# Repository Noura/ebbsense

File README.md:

# EBB Sense
  Controlling a wearable display using a bitalino EDA sensor

### Software
- Arduino Code

### Serial Graph for Debugging
- Graph the data from the arduino code running over Serial port
- Scale using up and down keys

### Hardware

- Eagle schematic and board
- Current version is 2.1

### Shirt

Each pinstripe had about 2-7Ω resistance and received about 450mA from a 3.7V LiPo battery via an Adafruit Powerboost 5V regulator, switching on (100% duty cycle) or off (0%) with a transistor controlled by Arduino pins. Each pinstripe consists of a single conductive thread. Snaps on the inside of the shirt provided removable but secure electrical connections to the thread endpoints. A Bitalino skin conductance sensor was placed on the back of the left shoulder of the shirt to hide the sensor from public view and secure it within the shirt. 

Fabric enclosures for electronics fit inside the shirt. (a) Skin conductance sensor with electrodes on colored paper for visibility. (b) Snaps connections to pinstripes. (c) Diagrammatic representation of pinstripes, which in actuality were sewn into shirt. (d) Snaps connections with FSRs for override on/off features. (e) Diagrammatic representation of FSRs, which in actuality were embedded in shirt seams. (f) PCB and battery, which were hidden in an interior shirt pocket.

---

### Team
- Noura Howell
- Laura Devendorf
- Rundong Tian
- Tomás Vega

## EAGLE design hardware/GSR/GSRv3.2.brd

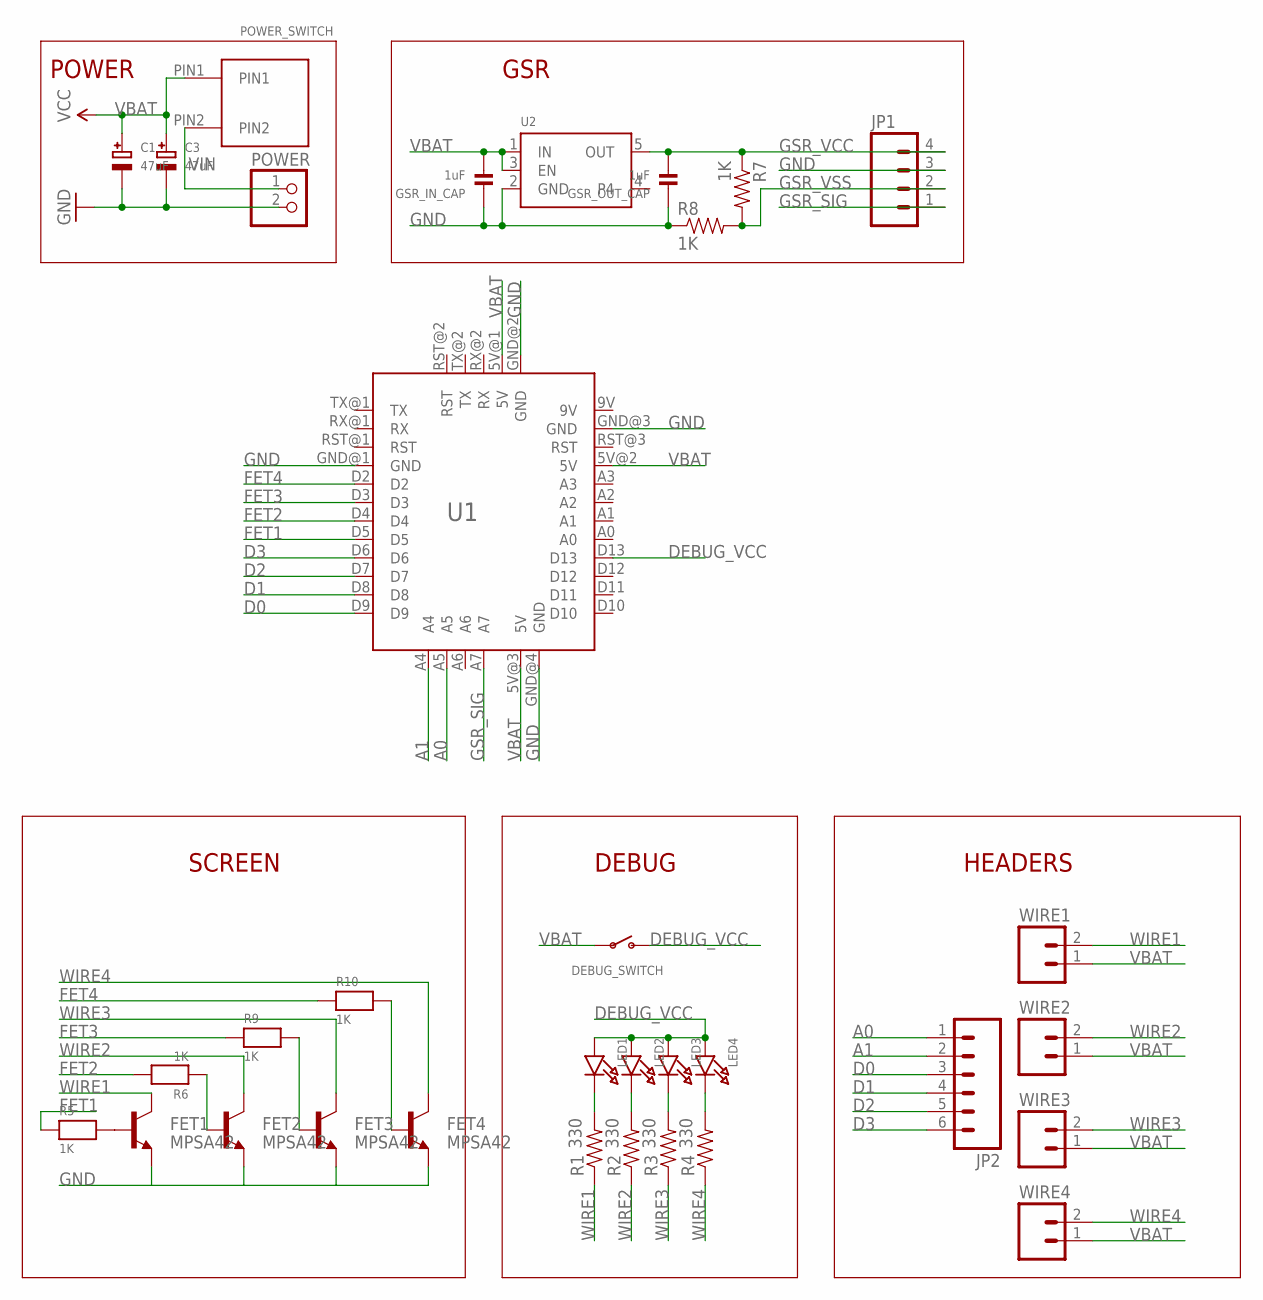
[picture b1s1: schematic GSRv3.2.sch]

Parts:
C1, C3: 47uF; EIA3528-21/B-W
DEBUG_SWITCH: SWITCH_SPST; SPST_SMT_19192
FET1, FET2, FET3, FET4: MPSA42; SOT23-3
GSR_IN_CAP: 1uF; 0603
GSR_OUT_CAP: 1uF; 0603
JP1: M04POLAR; MOLEX-1X4
JP2: M06SILK_FEMALE_PTH; 1X06
LED1, LED2, LED3, LED4: LED0603_NOOUTLINE; CHIPLED_0603_NOOUTLINE
POWER: JST_2PIN; JSTPH2
POWER_SWITCH: PUSH_BUTTON
R1, R2, R3, R4: 330; 0603-RES
R5, R6, R7, R8, R9, R10: 1K; 0603
U1: ARDUINO_MINI
U2: VREG_SOT23-5; SOT23-5
WIRE1, WIRE2, WIRE3, WIRE4: M02POLAR; MOLEX-1X2

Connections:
9V: U1.9V
A0: JP2.1, U1.A5
A1: JP2.2, U1.A4
D0: JP2.3, U1.D9
D1: JP2.4, U1.D8
D2: JP2.5, U1.D7
D3: JP2.6, U1.D6
DEBUG_VCC: DEBUG_SWITCH.C (S), LED1.A, LED2.A, LED3.A, LED4.A, U1.D13
FET1: R5.1, U1.D5
FET2: R6.2, U1.D4
FET3: R9.1, U1.D3
FET4: R10.1, U1.D2
GND: C1.-, C3.-, FET1.2 (E), FET2.2 (E), FET3.2 (E), FET4.2 (E), GSR_IN_CAP.1, GSR_OUT_CAP.1, JP1.3, POWER.2, R8.1, U1.GND@1 (GND), U1.GND@2 (GND), U1.GND@3 (GND), U1.GND@4 (GND), U2.2 (GND)
GSR_SIG: JP1.1, U1.A7
GSR_VCC: GSR_OUT_CAP.2, JP1.4, R7.1, U2.5 (OUT)
GSR_VSS: JP1.2, R7.2, R8.2
unnamed: LED1.C, R1.2
unnamed: LED2.C, R2.2
unnamed: LED3.C, R3.2
unnamed: LED4.C, R4.2
unnamed: FET1.1 (B), R5.2
unnamed: FET2.1 (B), R6.1
unnamed: FET3.1 (B), R9.2
unnamed: FET4.1 (B), R10.2
VBAT: C1.+, C3.+, DEBUG_SWITCH.B, GSR_IN_CAP.2, POWER_SWITCH.PIN1, U1.5V@1 (5V), U1.5V@2 (5V), U1.5V@3 (5V), U2.1 (IN), U2.3 (EN), WIRE1.1, WIRE2.1, WIRE3.1, WIRE4.1
VIN: POWER.1, POWER_SWITCH.PIN2
WIRE1: FET1.3 (C), R1.1, WIRE1.2
WIRE2: FET2.3 (C), R2.1, WIRE2.2
WIRE3: FET3.3 (C), R3.1, WIRE3.2
WIRE4: FET4.3 (C), R4.1, WIRE4.2

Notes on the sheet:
DEBUG
SCREEN
HEADERS
POWER
GSR

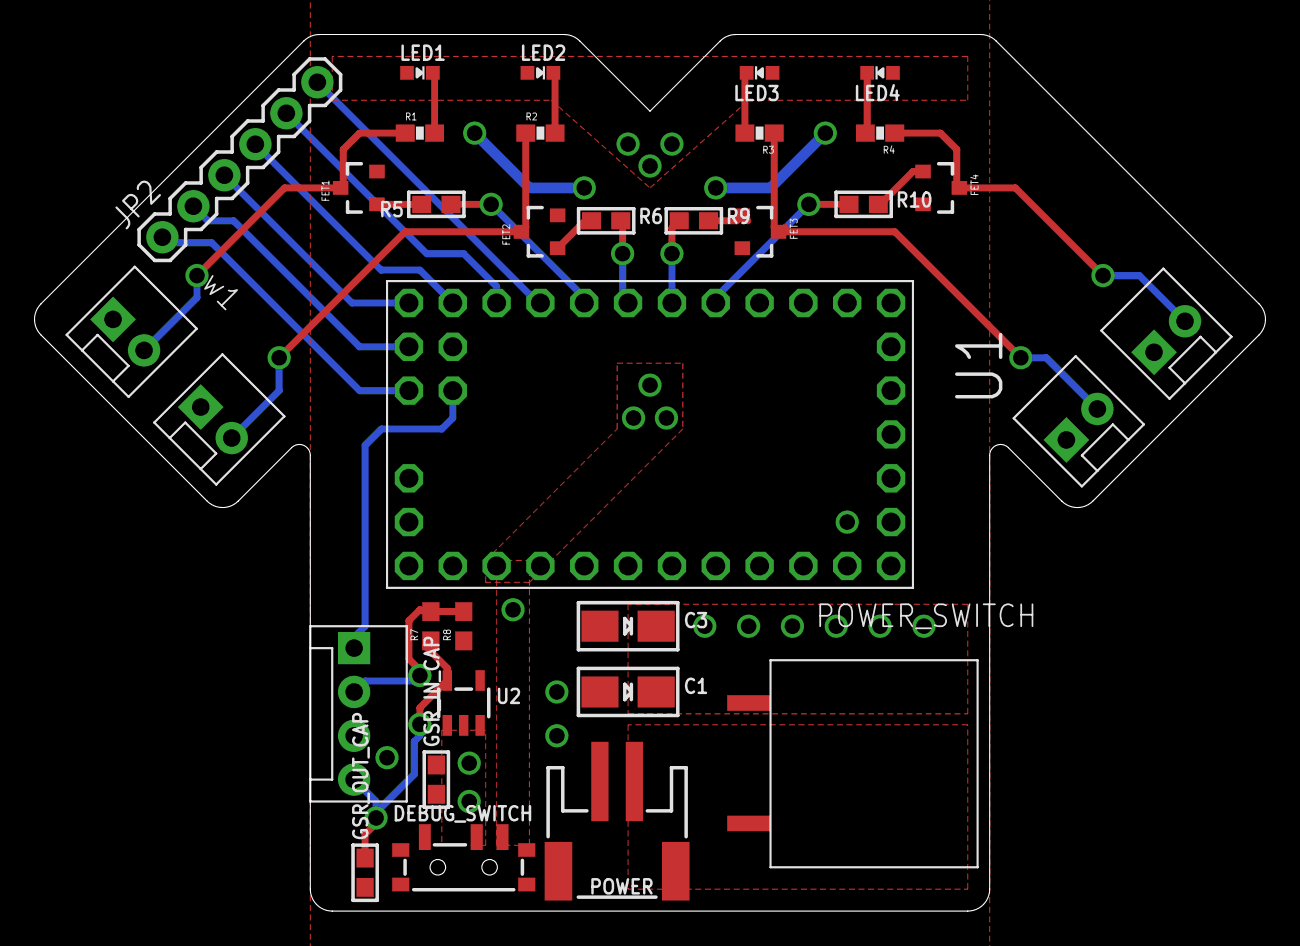
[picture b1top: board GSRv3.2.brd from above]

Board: 2 copper layers, 71.3 x 50.8 mm, 33 parts (0 on the bottom side), 29 nets.

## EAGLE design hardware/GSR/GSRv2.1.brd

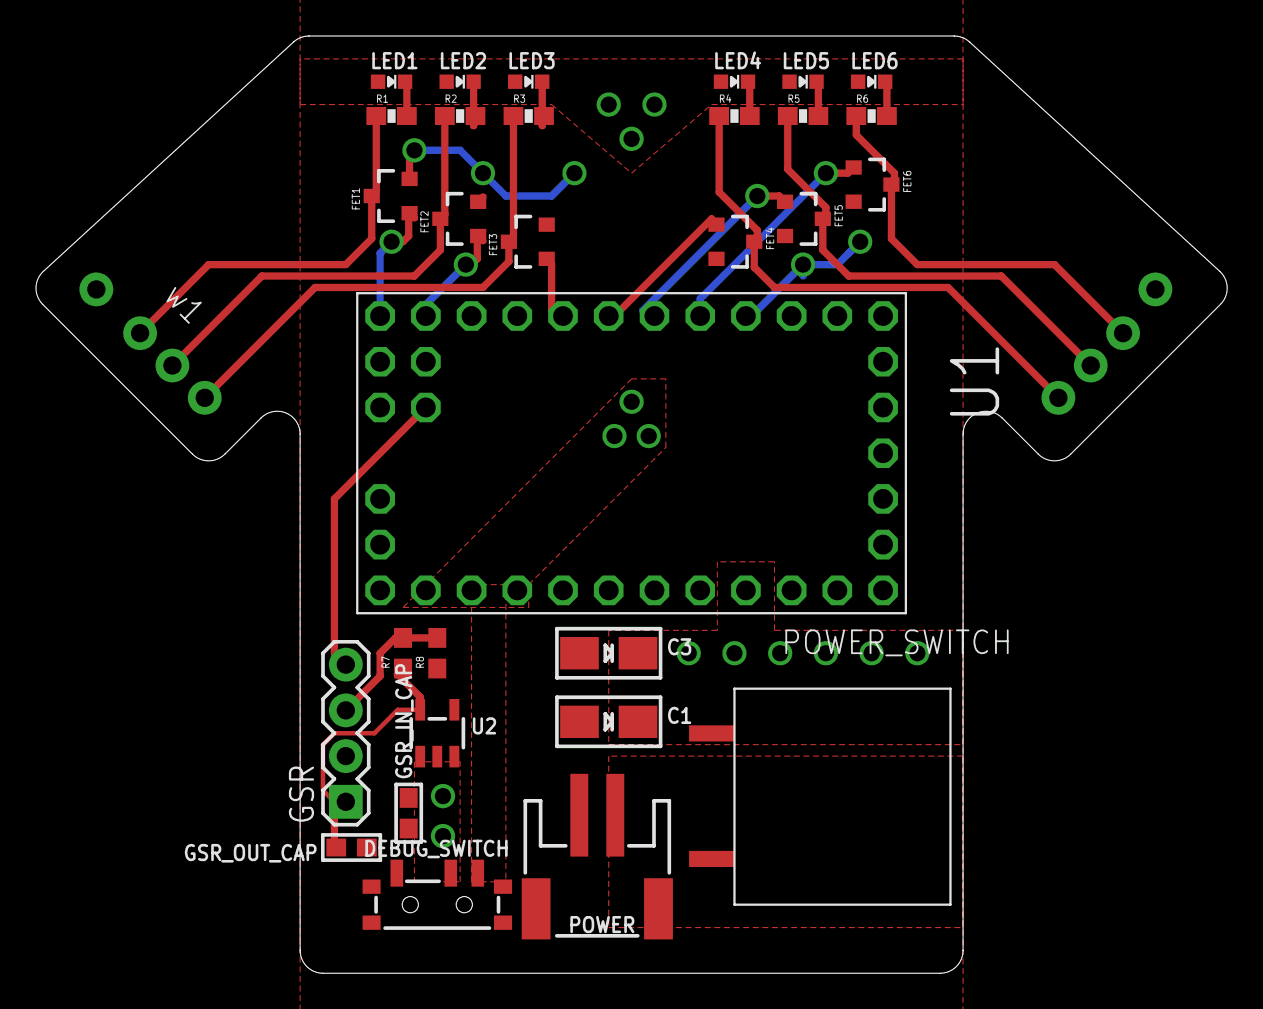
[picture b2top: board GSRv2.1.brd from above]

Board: 2 copper layers, 66.2 x 52.1 mm, 38 parts (0 on the bottom side), 25 nets.

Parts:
C1, C3: EIA3528-21/B-W
DEBUG_SWITCH: SPST_SMT_19192
FET1, FET2, FET3, FET4, FET5, FET6: MPSA42; SOT23-3
GSR: 1X04
GSR_IN_CAP: 1uF; 0603
GSR_OUT_CAP: 1uF; 0603
LED1, LED2, LED3, LED4, LED5, LED6: CHIPLED_0603_NOOUTLINE
POWER: JSTPH2
POWER_SWITCH: PUSH_BUTTON
R1, R2, R3, R4, R5, R6: 330; 0603-RES
R7, R8: 330; 0603
U1: ARDUINO_MINI
U2: SOT23-5
VBAT@1, VBAT@2: 1X01NS-KIT
W1, W2, W3, W4, W5, W6: 1X01NS-KIT

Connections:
DEBUG_VCC: DEBUG_SWITCH.C, LED1.A, LED2.A, LED3.A, LED4.A, LED5.A, LED6.A, U1.D13
FET1: FET1.1, U1.D9
FET2: FET2.1, U1.D8
FET3: FET3.1, U1.D5
FET4: FET4.1, U1.D4
FET5: FET5.1, U1.D3
FET6: FET6.1, U1.D2
GND: C1.-, C3.-, FET1.2, FET2.2, FET3.2, FET4.2, FET5.2, FET6.2, GSR.2, GSR_IN_CAP.1, GSR_OUT_CAP.1, POWER.2, R8.1, U1.GND@1, U1.GND@2, U1.GND@3, U1.GND@4, U2.2
GSR_SIG: GSR.4, U1.A7
GSR_VCC: GSR.1, GSR_OUT_CAP.2, R7.1, U2.5
GSR_VSS: GSR.3, R7.2, R8.2
unnamed: LED1.C, R1.2
unnamed: LED2.C, R2.2
unnamed: LED3.C, R3.2
unnamed: LED4.C, R4.2
unnamed: LED5.C, R5.2
unnamed: LED6.C, R6.2
VBAT: C1.+, C3.+, DEBUG_SWITCH.B, GSR_IN_CAP.2, POWER_SWITCH.PIN1, U1.5V@1, U1.5V@2, U1.5V@3, U2.1, U2.3, VBAT@1.1, VBAT@2.1
VIN: POWER.1, POWER_SWITCH.PIN2
WIRE1: FET1.3, R1.1, W1.1
WIRE2: FET2.3, R2.1, W2.1
WIRE3: FET3.3, R3.1, W3.1
WIRE4: FET4.3, R4.1, W4.1
WIRE5: FET5.3, R5.1, W5.1
WIRE6: FET6.3, R6.1, W6.1

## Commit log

2015-10-29 readme
2015-10-29 adding basic filter code and processing serial graph
2015-10-29 added credit in serial graph script
2015-10-29 adding link to the filter library we are using
2015-10-30 changing to a different low pass filter with a cutoff around 0.4 Hz, and getting the serial graph to mark lines to show the peaks
2015-11-01 changed to doing spike detection based on average and standard deviation. when the current value is more than 1 standard deviation away from the average, that counts as a spike.
2015-11-01 changed the graphing so that it only draws a point when there is a new point coming in, rather than every time processing calls the draw function repeatedly. also fixed the way we were drawing marks 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
2015-11-03 added a comment to explain an if statement
2015-11-03 trying out using a class to control the threads.
2015-11-03 decided not to use a class to control the threads individually. it helps for each thread to know about each other so they don't all try to draw power at the same time.
2015-11-04 thread management
2015-11-04 thread controls works for any number of output pwm pins now
2015-11-04 calibrating to the triangle we have
2015-11-05 replaced NPINS with NTHREADS for clarity
2015-11-05 when in debug mode, show LEDs going on / off corresponding to when threads are activated.
2015-11-05 added comments.
2015-11-09 added hardware and updated readme
2015-11-09 .DS_Store banished!
2015-11-11 better printing of serial ports list in processing sketch
2015-11-11 messing with threads settings
2015-11-11 debug mode and capping the filtered gsr values and a minimum threshold for what counts as a peak
2015-11-11 the code for the PCB is slightly different than the code for the breadboard arduino so they are diferent sketches now
2015-11-14 v3.0
2015-11-20 added code for wearablePCB
2015-12-08 tweaking calibration
2015-12-08 wearableOneThread is a simplified version for when there is only one thread. less code is better
2016-03-09 changing the thread on time to 3 minutes
2016-03-09 second serial graph monitor is good for watching 2 prototypes simultaneously
2016-03-16 renamed wearablePCB to wearableMultiThread because i think that name is more descriptive. also added a descriptive comment at the top.
2016-03-16 added button. pressing button forces peak, forcing power to thread.
2016-03-16 upped the peak threadshold. peaks must involve a GSR increase of at least 50 now, whereas before it was 25. hopefully this will solve an issue where what i think is some slight electrical noise (poss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
2016-03-16 wearablePCB
2016-03-31 changing sensor pin to A5
2016-03-31 deleting wearablePCB because it has been renamed to wearableMultiThread because that name is more descriptive
2016-04-25 GSR3.2
2016-06-23 ignoring files that i think are just related to my view settings in eagle
2016-06-23 printing raw sensor value instead of filtered sensor value
2016-06-23 code for the SmarTee PCB in summer 2016. adapted to have more features than previous iterations
2016-06-23 fixed typo
2016-06-28 it activates each thread in turn now when a Moment (caused by an EDA spike or touching one of the FSR sensors) is logged
2016-06-29 turning off ALL thread pins at setup, not just the thread pins we are currently using.
2016-07-12 updating pins and thread power and timing settings. adding comments
2016-07-12 added TODO comment
2016-07-12 touching the FSR off deletes all moments
2016-07-26 added comment explaining MOMENT_DT
2016-07-26 upping power settings at the last minute for the pilot study
2016-07-26 adding a print statement for edaVal
2017-09-10 adding pcb image to github
2017-09-10 fixing link to image
2017-09-10 adding some more technical details about the shirt
2017-09-10 adding more details to README
2017-09-10 fixing image link
2017-09-10 fixing typos
2017-09-10 fixing typo in filename

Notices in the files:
parts and their libraries:
microbuilder: This work is placed in the public domain, and may be freely used for commercial and non-commercial work with the following conditions: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
SparkFun-DiscreteSemi: Licensing: Creative Commons ShareAlike 4.0 International - https://creativecommons.org/licenses/by-sa/4.0
